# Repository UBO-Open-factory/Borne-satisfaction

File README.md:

# The project #
This french project consists in making a terminal with 3 push buttons that can record the data on an SD card to collect results for a satisfaction survey.

You can find the project's page on [wikifactory](https://wikifactory.com/+uboopenfactory/borne-de-satisfaction)

Last : most of the documentation is written in French...

# Directory structure #

## Electronique
You can find here the Eagles project and everything about the mother board constuction.

## Mécanique
You can find here everything about the constuction of the wood-box as Lasercut plans.

Plans are on SVG format.

## Programmation
This is where you will find the main program, tests and everything about the ESP-32 code.

Code is written in C++ Language for a Firebeetle ESP32. Please [check the documentation before compiling](./Programmation/Microcontroleur/README.md).

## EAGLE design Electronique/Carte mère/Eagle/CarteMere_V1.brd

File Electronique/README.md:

L'électronique de la borne de satisfaction s'articule autour de l'architecture composée :
- Une carte Firebeetle ESP32 (Processeur+Charge de la batterie) <br>
- 3 Boutons poussoirs pour le vote
- 3 Leds pour indiquer le bouton pressé au votant
- Un lecteur de carte SD et sa carte SD qui contient les résultats des votes
- Une horloge temps réelle pour indiquer l'horodatage des votes

### Architecture Principale ###

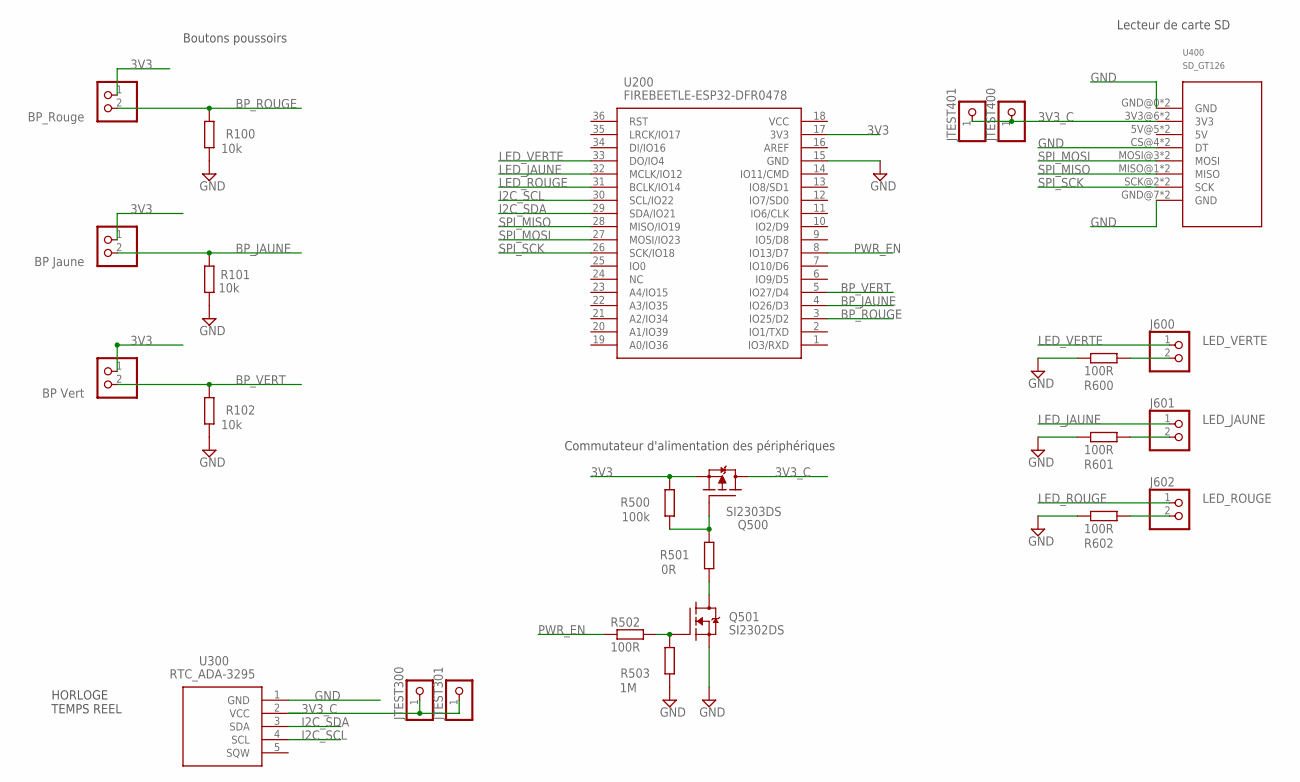
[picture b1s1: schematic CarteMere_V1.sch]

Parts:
J100: BP_Rouge; 1X02
J101: BP Jaune; 1X02
J102: BP Vert; 1X02
J600: LED_VERTE; 1X02
J601: LED_JAUNE; 1X02
J602: LED_ROUGE; 1X02
JTEST300, JTEST301, JTEST400, JTEST401: PINHD-1X1; 1X01
Q500: SI2303DS; SOT23
Q501: SI2302DS; SOT23
R100, R101, R102: 10k; 0207/10
R500: 100k; 0207/10
R501: 0R; 0207/10
R502, R600, R601, R602: 100R; 0207/10
R503: 1M; 0207/10
U200: FIREBEETLE-ESP32-DFR0478; FIREBEETLE_ESP32
U300: RTC_ADA-3295; ADA3295
U400: SD_GT126

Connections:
3V3: J100.1, J101.1, J102.1, Q500.2 (S), R500.2, U200.17 (3V3)
3V3_C: JTEST300.1, JTEST301.1, JTEST400.1, JTEST401.1, Q500.3 (D), U300.2 (VCC), U400.3V3@6 (3V3), U400.3V3@9 (3V3)
BP_JAUNE: J101.2, R101.2, U200.4 (IO26/D3)
BP_ROUGE: J100.2, R100.2, U200.3 (IO25/D2)
BP_VERT: J102.2, R102.2, U200.5 (IO27/D4)
DQ501: Q501.3 (D), R501.1
GND: Q501.2 (S), R100.1, R101.1, R102.1, R503.1, R600.1, R601.1, R602.1, U200.15 (GND), U300.1 (GND), U400.CS@4 (DT), U400.CS@11 (DT), U400.GND@0 (GND), U400.GND@7 (GND), U400.GND@8 (GND), U400.GND@15 (GND)
I2C_SCL: U200.30 (SCL/IO22), U300.4 (SCL)
I2C_SDA: U200.29 (SDA/IO21), U300.3 (SDA)
LED_JAUNE: J601.1, U200.32 (MCLK/IO12)
LED_ROUGE: J602.1, U200.31 (BCLK/IO14)
LED_VERTE: J600.1, U200.33 (DO/IO4)
unnamed: Q501.1 (G), R502.2, R503.2
unnamed: J600.2, R600.2
unnamed: J601.2, R601.2
unnamed: J602.2, R602.2
unnamed: Q500.1 (G), R500.1, R501.2
PWR_EN: R502.1, U200.8 (IO13/D7)
SPI_MISO: U200.28 (MISO/IO19), U400.MISO@1 (MISO), U400.MISO@14 (MISO)
SPI_MOSI: U200.27 (MOSI/IO23), U400.MOSI@3 (MOSI), U400.MOSI@12 (MOSI)
SPI_SCK: U200.26 (SCK/IO18), U400.SCK@2 (SCK), U400.SCK@13 (SCK)

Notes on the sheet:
HORLOGE TEMPS REEL
Commutateur d'alimentation des périphériques
Lecteur de carte SD
Boutons poussoirs

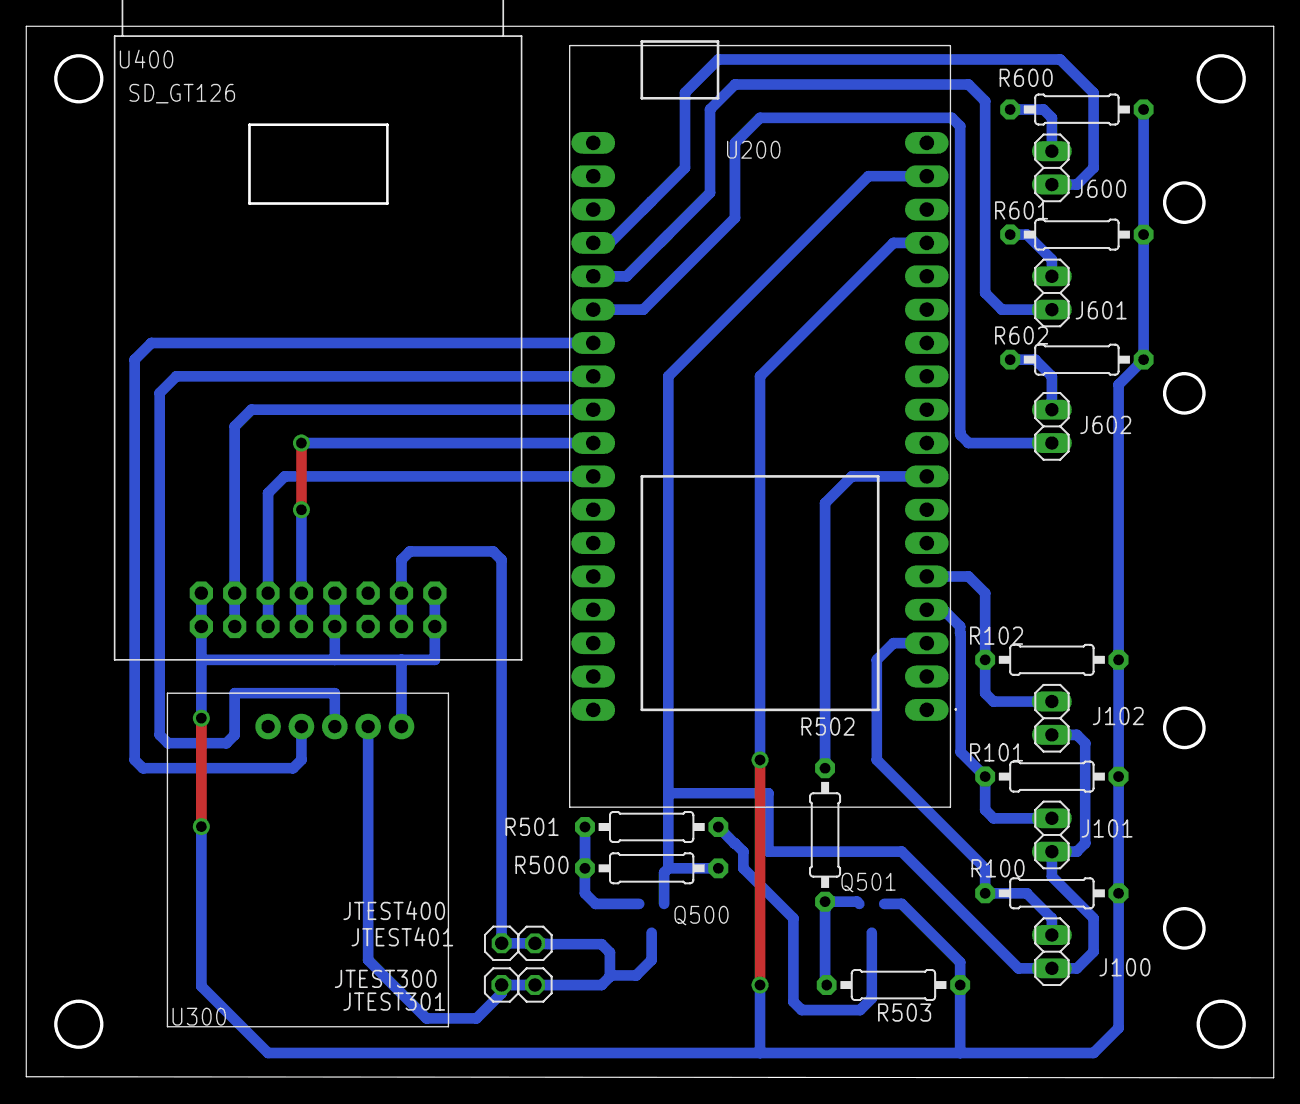
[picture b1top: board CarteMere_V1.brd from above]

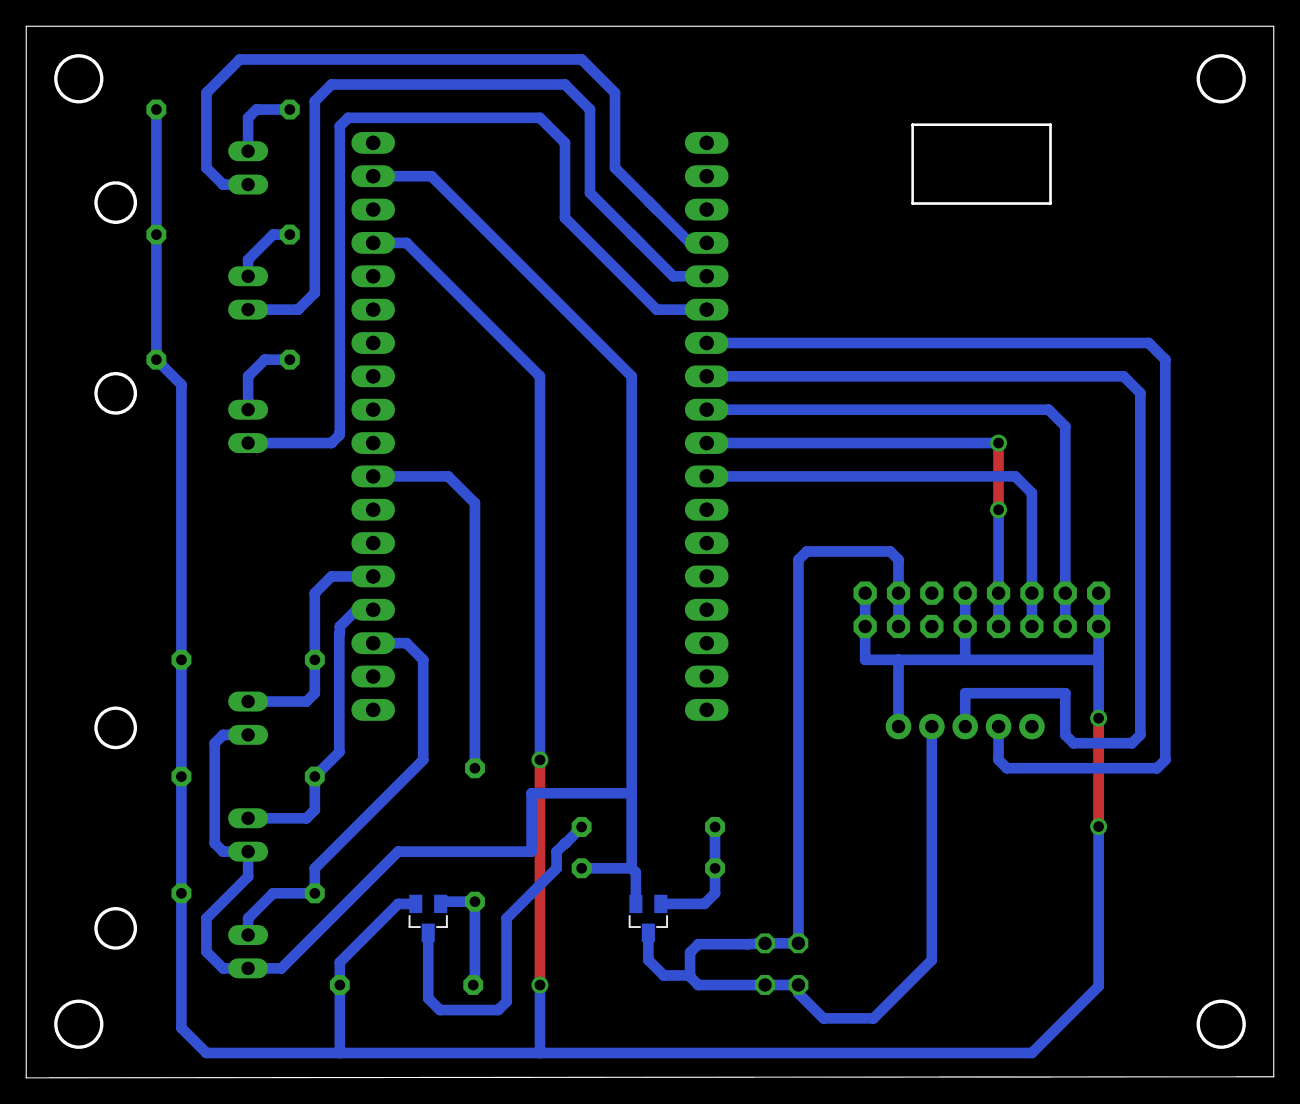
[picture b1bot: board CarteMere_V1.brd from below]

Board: 2 copper layers, 94.7 x 79.8 mm, 25 parts (2 on the bottom side), 21 nets.

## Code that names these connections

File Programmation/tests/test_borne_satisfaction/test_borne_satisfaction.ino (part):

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#define ON HIGH
#define OFF LOW

#define PIN_LED_VERTE 4
#define PIN_LED_JAUNE 12
#define PIN_LED_ROUGE 14

#define PIN_BP_VERT 27
#define PIN_BP_JAUNE 26
#define PIN_BP_ROUGE 25

#define PIN_PWR_EN 13

#define TIMEOUT_TEST_BP 10000 // en ms

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  delay(100);

  // initialisation des E/S
  pinMode (PIN_LED_VERTE,OUTPUT);
  pinMode (PIN_LED_JAUNE,OUTPUT);
  pinMode (PIN_LED_ROUGE,OUTPUT);
  led(VERT,OFF);
  led(JAUNE,OFF);
  led(ROUGE,OFF);
  
  pinMode (PIN_BP_VERT,INPUT);
  pinMode (PIN_BP_JAUNE,INPUT);
  pinMode (PIN_BP_ROUGE,INPUT);

  pinMode(PIN_PWR_EN,OUTPUT);
  peripheriques(OFF);
  
  // début du test
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    debut = millis();
    res=false;
    while (millis() - debut < TIMEOUT_TEST_BP) {
      if (digitalRead(PIN_BP_VERT) == HIGH) {
        res=true;
        break;
      }
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    debut = millis();
    res=false;
    while (millis() - debut < TIMEOUT_TEST_BP) {
      if (digitalRead(PIN_BP_JAUNE) == HIGH) {
        res=true;
        break;
      }
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    debut = millis();
    res=false;
    while (millis() - debut < TIMEOUT_TEST_BP) {
      if (digitalRead(PIN_BP_ROUGE) == HIGH) {
        res=true;
        break;
      }
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}

void led( byte couleur, bool etat) {
  if (couleur == VERTE) digitalWrite (PIN_LED_VERTE,etat);
  if (couleur == VERT)  digitalWrite (PIN_LED_VERTE,etat);
  if (couleur == JAUNE) digitalWrite (PIN_LED_JAUNE,etat);
  if (couleur == ROUGE) digitalWrite (PIN_LED_ROUGE,etat);
}

void peripheriques(bool etat) {
  // alimentation des périphériques
  digitalWrite(PIN_PWR_EN,etat);
  delay(20); // pour laisser à l'alimentation le temps de s'établir 20 ms mini
  if (etat) {
    Serial.println ("Alimentation des périphériques ON");
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
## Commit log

2022-05-31 Version initiale

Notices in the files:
Programmation/tests/test_borne_satisfaction/test_borne_satisfaction.ino:
License : CC - BY - SA
